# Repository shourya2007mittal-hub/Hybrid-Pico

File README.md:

# Hybrid-Pico

So I have designed an RP2040 based Devboard with identical dimensions and pin layout as a A Raspberry Pi Pico . <br>
The board contains the same pin layout and dimensions the RP Pico .<br>
These is a Boot pin for reboot and few onboard LEDS and 3.3V Voltage regulator for power supply to the micro-controllers. <br>
and my design has an upgrade . The Dev-board also includes an inbuilt IMU and Barometer . This broadens the scope of use for this board . As it could be easily connected  to a breadboard and the inbuilt IMU/Barometer sensors helps a lot in during  prototyping a project like a handheld with Gyro , a movement sensor device or  as a  compass or as a flight controller

## Features

- Based on RP-2040 Chip
- Identical Dimension and pin layout as RP-PICO
- 40 physical pins + 3 debugs pin and the board is breadboard compatible 
- Has inbuilt 3.3V  Voltage regulator
- has Inbuilt IMU (MPU-5060) and Barometer (BMP280)

  # Project Bill of Materials (BOM) & Cost Breakdown

This repository contains the hardware components, PCB fabrication, and assembly service details for the project.

---

## 🛠️ Bill of Materials (Components)

| Component / Comment | Quantity | Price (USD) | JLCPCB Part Link |
| :--- | :---: | :---: | :--- |
| **1uF** | 8 | $0.61 | [GRM033R61A105ME44D](https://jlcpcb.com/partdetail/MurataElectronics-GRM033R61A105ME44D/C76935) |
| **10uF** | 16| $0.59 | [CL10A106MQ8NNNC](https://jlcpcb.com/partdetail/2043-CL10A106MQ8NNNC/C1691) |
| **33pF** | 8 | $0.11 | [GRM0335C1H330JA01D](https://jlcpcb.com/partdetail/MurataElectronics-GRM0335C1H330JA01D/C76925) |
| **0.1uF** | 12| $0.15 | [0201X104K100NT](https://jlcpcb.com/partdetail/270391-0201X104K100NT/C284966) |
| **27 ohm** | 4 | $0.15 | [0201X104K100NT](https://jlcpcb.com/partdetail/25843-0402WGF270JTCE/C25100) |
| **100nF** | 8| $0.15 | [GRM033R61A104KE15D](https://jlcpcb.com/partdetail/MurataElectronics-GRM033R61A104KE15D/C76934) |
| **LED** | 6 | $0.68 | [XL0201SURC](https://jlcpcb.com/partdetail/XINGLIGHT-XL0201SURC/C3646923) |
| **USB_C_Receptacle_USB2.0_16P** | 2 | $4.08 | [USB31_TYPE_CFSABC](https://jlcpcb.com/partdetail/GSwitch-GT_USB7010ASV/C2988369) |
| **33R** | 20 | $0.06 | [0201WMJ0330TEE](https://jlcpcb.com/partdetail/416306-0201WMJ0330TEE/C423356) |
| **50K** | 6 | $0.76 | [GL3549](https://jlcpcb.com/partdetail/10622-GL3549/C10083) |
| **1K** | 22 | $0.06 | [0201WMF1001TEE](https://jlcpcb.com/partdetail/259895-0201WMF1001TEE/C270365) |
| **SW_Push** | 4 | $1.86 | [K5_1672SN01](https://jlcpcb.com/partdetail/Korean_HropartsElec-K5_1672SN01/C502360) |
| **MCP1700x-330xxTT** | 2 | $1.03 | [MCP1700_3002ETO](https://jlcpcb.com/partdetail/MicrochipTech-MCP1700T_3302ETT/C39051) |
| **MPU-6050** | 2 | $26.80 | [MPU6050](https://jlcpcb.com/partdetail/TDKInvenSense-MPU6050/C24112) |
| **BMP280** | 2 | $25.58 | [BMP280](https://jlcpcb.com/partdetail/BoschSensortec-BMP280/C83291) |
| **12MHz** | 5 | $1.27 | [NX3225GA_12MHZ](https://jlcpcb.com/partdetail/NDK-NX3225GA_12MHZ_STD_CRG2/C481407) |
| **RP2040** | 0 | $2.47 | [RP2040](https://jlcpcb.com/partdetail/RaspberryPi-RP2040/C2961140) |
| **W25Q16JVUXIQTR** | 2 | $0.987 | [W25Q16JVUXIQTR](https://jlcpcb.com/partdetail/WinbondElec-W25Q16JVUXIQTR/C5333738) |

---

## ⚙️ Fabrication & Assembly Fees

| Service Description | Quantity | Price (USD) |
| :--- | :---: | :---: |
| PCB Fabrication (5 pcs) | 1 | $4.00 |
| PCBA Setup Fee | 1 | $25.56 |
| PCBA Stencil Fee | 1 | $8.21 |
| Feeders Loading Fee | 1 | $19.89 |
| SMT Assembly Fee | 1 | $0.76 |
| Hand-soldering Labor Fee | 1 | $3.58 |
| Manual Assembly Fee | 1 | $0.64 |
| PCB Assembly Fixture | 1 | $16.42 |
| Special Components Fee | 1 | $0.06 |
| Packaging Fee | 1 | $0.49 |
| Shipping Fee | 1 | $11.68 |

---

## 💰 Total Cost

- **Grand Total:** **`$138.29 USD`**

### Schematic 

### PCB Design

### 3D Design

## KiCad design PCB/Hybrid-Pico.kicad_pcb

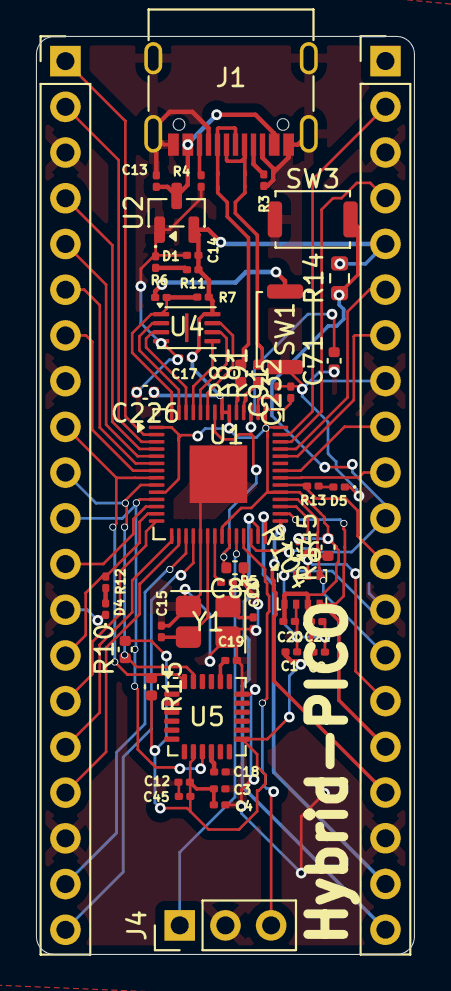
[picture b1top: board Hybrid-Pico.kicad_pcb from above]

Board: 2 copper layers, 21.0 x 51.0 mm, 50 parts (0 on the bottom side), 58 nets.

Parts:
C1: 1uF; C_0201_0603Metric
C2, C3, C4, C17: 0.1uF; C_0201_0603Metric
C12: 10 uf; C_0201_0603Metric
C13, C14: 10uF; C_0201_0603Metric
C15, C16: 33pF; C_0201_0603Metric
C18, C19: 0.1uf; C_0201_0603Metric
C20, C21, C232: 100 nf; C_0201_0603Metric
C45: 0.1 uf; C_0201_0603Metric
C71: 1uF; C_0402_1005Metric
C88, C226: 100 nf; C_0402_1005Metric
C91: 1uf; C_0201_0603Metric
D1, D4, D5: LED; LED_0201_0603Metric
J1: USB_C_Receptacle_USB2.0_16P; USB_C_Receptacle_G-Switch_GT-USB-7010ASV
J2, J3: Conn_01x20; PinHeader_1x20_P2.54mm_Vertical
J4: Conn_01x03; PinHeader_1x03_P2.54mm_Vertical
R3, R4: 50K; C_0201_0603Metric
R5, R6, R11, R12, R13: 1K; C_0201_0603Metric
R7: 10K; C_0201_0603Metric
R10, R15, R104, R145: 5.1K; C_0402_1005Metric
R14: 10K; R_0603_1608Metric
R81, R91: 27; C_0402_1005Metric
SW1, SW3: SW_Push; SW_Push_SPST_NO_Alps_SKRK
U1: RP2040; QFN-56-1EP_7x7mm_P0.4mm_EP3.2x3.2mm
U2: MCP1700x-330xxTT; SOT-23
U4: W25Q16JVUXIQ TR; Winbond_USON-8-1EP_3x2mm_P0.5mm_EP0.2x1.6mm
U5: MPU-6050; InvenSense_QFN-24_4x4mm_P0.5mm
U6: BMP280; Bosch_LGA-8_2x2.5mm_P0.65mm_ClockwisePinNumbering
Y1: 12 MHz; Crystal_SMD_3225-4Pin_3.2x2.5mm

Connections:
3.3V: C1.1, C2.1, C3.1, C4.1, C12.1, C14.1, C17.1, C20.1, C21.1, C45.1, C91.1, C226.1, C232.1, J3.5, R7.2, R11.1, R14.2, R104.2, R145.2, U1.1 (IOVDD), U1.10 (IOVDD), U1.22 (IOVDD), U1.33 (IOVDD), U1.42 (IOVDD), U1.43 (ADC_AVDD), U1.44 (VREG_IN), U1.48 (USB_VDD), U1.49 (IOVDD), U2.2 (VO), U4.8 (VCC), U5.8 (VLOGIC), U5.13 (VDD), U6.6 (VDDIO), U6.8 (VDD)
5V: C13.1, J1.A4 (VBUS), J1.A9 (VBUS), J1.B4 (VBUS), J1.B9 (VBUS), U2.3 (VI)
+3.3V: R10.2, R15.2
AD1: J2.11, U1.11 (GPIO8), U5.9 (AD0)
AD2: J3.16, U1.30 (GPIO19), U6.5 (SDO)
GND: C1.2, C2.2, C3.2, C4.2, C12.2, C13.2, C14.2, C15.1, C16.1, C17.2, C18.2, C19.2, C20.2, C21.2, C45.2, C71.1, C88.1, C91.2, C226.2, C232.2, D1.1 (K), D4.1 (K), D5.1 (K), J1.A1 (GND), J1.A8 (SBU1), J1.A12 (GND), J1.B1 (GND), J1.B8 (SBU2), J1.B12 (GND), J1.S1 (SHIELD), J2.3, J2.8, J2.13, J2.18, J3.3, J3.8, J3.13, J3.18, J4.2, R3.2, R4.2, SW1.1, SW3.1, U1.19 (TESTEN), U1.57 (GND), U2.1 (GND), U4.4 (GND), U5.18 (GND), U6.1 (GND), U6.7 (GND), Y1.2, Y1.4
GPIO0: J2.1, U1.2 (GPIO0)
GPIO1: J2.2, U1.3 (GPIO1)
GPIO2: J2.4, U1.4 (GPIO2)
GPIO3: J2.5, U1.5 (GPIO3)
GPIO4: J2.6, U1.6 (GPIO4)
GPIO5: J2.7, U1.7 (GPIO5)
GPIO6: J2.9, R15.1, U1.8 (GPIO6), U5.24 (SDA)
GPIO7: J2.10, R10.1, U1.9 (GPIO7), U5.23 (SCL)
GPIO9: J2.12, U1.12 (GPIO9)
GPIO10: J2.14, R12.1, U1.13 (GPIO10)
GPIO11: J2.15, U1.14 (GPIO11)
GPIO12: J2.16, U1.15 (GPIO12)
GPIO13: J2.17, U1.16 (GPIO13)
GPIO14: J2.19, U1.17 (GPIO14)
GPIO15: J2.20, U1.18 (GPIO15)
GPIO16: J3.20, U1.27 (GPIO16)
GPIO17: J3.19, U1.28 (GPIO17)
GPIO18: J3.17, U1.29 (GPIO18)
GPIO20: J3.15, R104.1, U1.31 (GPIO20), U6.3 (SDI)
GPIO21: J3.14, R145.1, U1.32 (GPIO21), U6.4 (SCK)
GPIO22: J3.12, R13.1, U1.34 (GPIO22)
GPIO23: J3.10, U1.35 (GPIO23)
GPIO24: J3.9, U1.36 (GPIO24)
GPIO26_ADC0: J3.7, U1.38 (GPIO26_ADC0)
GPIO27_ADC1: J3.6, U1.39 (GPIO27_ADC1)
GPIO28_ADC2: J3.4, U1.40 (GPIO28_ADC2)
GPIO29_ADC3: J3.2, U1.41 (GPIO29_ADC3)
unnamed: C16.2, R5.1, Y1.1
unnamed: D1.2 (A), R11.2
unnamed: D4.2 (A), R12.2
unnamed: D5.2 (A), R13.2
unnamed: J1.A5 (CC1), R3.1
unnamed: J1.B5 (CC2), R4.1
unnamed: J1.A6 (D+), J1.B6 (D+)
unnamed: J1.A7 (D-), J1.B7 (D-)
unnamed: R6.2, SW1.2
unnamed: C88.2, U1.23 (DVDD), U1.45 (VREG_VOUT), U1.50 (DVDD)
unnamed: C19.1, U5.20 (CPOUT)
unnamed: C18.1, U5.10 (REGOUT)
QSPI_SCLK: U1.52 (QSPI_SCLK), U4.6 (CLK)
QSPI_SD0: U1.53 (QSPI_SD0), U4.5 (DI/IO_{0})
QSPI_SD1: U1.55 (QSPI_SD1), U4.2 (DO/IO_{1})
QSPI_SD2: U1.54 (QSPI_SD2), U4.3 (~WP/IO_{2})
QSPI_SD3: U1.51 (QSPI_SD3), U4.7 (~HOLD/~RESET/IO_{3})
QSPI_SS: R6.1, R7.1, U1.56 (QSPI_SS), U4.1 (~CS)
RUN: J3.11, SW3.2, U1.26 (RUN)
SWCLK: J4.1, U1.24 (SWCLK)
SWD: J4.3, U1.25 (SWD)
XIN: C15.2, U1.20 (XIN), Y1.3
XOUT: R5.2, U1.21 (XOUT)
_D+: R81.1, U1.47 (USB_DP)
_D-: R91.1, U1.46 (USB_DM)

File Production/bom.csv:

Designator,Footprint,Quantity,Value,LCSC Part #
"C1, C91",0201,2,1uF,
C12,0201,1,10 uf,
"C13, C14",0201,2,10uF,
"C15, C16",0201,2,33pF,
"C17, C18, C19, C2, C3, C4",0201,6,0.1uF,
"C20, C21, C232",0201,3,100 nf,
"C226, C88",0402,2,100 nf,
C45,0201,1,0.1 uf,
C71,0402,1,1uF,
"D1, D4, D5",0201,3,LED,
J1,USB_C_Receptacle_G-Switch_GT-USB-7010ASV,1,USB_C_Receptacle_USB2.0_16P,
"J2, J3",PinHeader_1x20_P2.54mm_Vertical,2,Conn_01x20,
J4,PinHeader_1x03_P2.54mm_Vertical,1,Conn_01x03,
"R10, R104, R145, R15",0402,4,4.7K,
"R11, R12, R13, R5, R6",0201,5,1K,
R14,0603,1,10K,
"R3, R4",0201,2,50K,
R7,0201,1,10K,
"R81, R91",0402,2,27,
"SW1, SW3",SW_Push_SPST_NO_Alps_SKRK,2,SW_Push,
U1,QFN-56-1EP_7x7mm_P0.4mm_EP3.2x3.2mm,1,RP2040,
U2,SOT-23,1,MCP1700x-330xxTT,
U4,Winbond_USON-8-1EP_3x2mm_P0.5mm_EP0.2x1.6mm,1,W25Q16JVUXIQ TR,
U5,InvenSense_QFN-24_4x4mm_P0.5mm,1,MPU-6050,
U6,Bosch_LGA-8_2x2.5mm_P0.65mm_ClockwisePinNumbering,1,BMP280,
Y1,Crystal_SMD_3225-4Pin_3.2x2.5mm,1,12 MHz,
